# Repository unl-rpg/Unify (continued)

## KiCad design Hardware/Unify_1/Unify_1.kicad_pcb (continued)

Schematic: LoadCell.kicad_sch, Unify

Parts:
C41, C42: 100n; C_0603_1608Metric
R101: 190k; R_0603_1608Metric
R102: 10k; R_0603_1608Metric
U30: INA321

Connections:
+5VA: C42.1, U30.7 (V+), U30.8 (SD); also elsewhere on the board
/Peripherals/LC_3_ADC: C41.1, R101.1, U30.6 (VOUT); also elsewhere on the board
/Peripherals/VREF: R102.2, U30.5 (REF); also elsewhere on the board
GND: C41.2, C42.2, U30.4 (V-); also elsewhere on the board
LC_3_NEG: U30.2 (VIN-); also elsewhere on the board
LC_3_POS: U30.3 (VIN+); also elsewhere on the board
unnamed: R101.2, R102.1, U30.1 (RG)

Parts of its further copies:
C37, C38, C39, C40: 100n; C_0603_1608Metric
R97, R99: 190k; R_0603_1608Metric
R98, R100: 10k; R_0603_1608Metric
U28, U29: INA321

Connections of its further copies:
+5VA: C38.1, C40.1, U28.7 (V+), U28.8 (SD), U29.7 (V+), U29.8 (SD); also elsewhere on the board
/Peripherals/LC_1_ADC: C37.1, R97.1, U28.6 (VOUT); also elsewhere on the board
/Peripherals/LC_2_ADC: C39.1, R99.1, U29.6 (VOUT); also elsewhere on the board
/Peripherals/VREF: R98.2, R100.2, U28.5 (REF), U29.5 (REF); also elsewhere on the board
GND: C37.2, C38.2, C39.2, C40.2, U28.4 (V-), U29.4 (V-); also elsewhere on the board
LC_1_NEG: U28.2 (VIN-); also elsewhere on the board
LC_1_POS: U28.3 (VIN+); also elsewhere on the board
LC_2_NEG: U29.2 (VIN-); also elsewhere on the board
LC_2_POS: U29.3 (VIN+); also elsewhere on the board
unnamed: R97.2, R98.1, U28.1 (RG)
unnamed: R99.2, R100.1, U29.1 (RG)

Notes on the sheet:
Calculations: Load Cell Rated Output: 1.5 +- 0.5 mV/V Load Cell Rated Output at 5V Supply: 5 - 10 mV (Calibrate in software) Nominal Load Cell Rated Output: 7.5mV So load cell will register a max 10mV differential signal at max load Instrumentation Amplifier Output: Vout = (Vin+ - Vin-) * Gain Inam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
+5V
Bridge
TAS606 Load Cell: Capacity: 50kg, 200kg (There are more) Rated Output: 1.5 +- 0.5 mV/V Excitation Voltage: 5-15V Output Resistance: 350 +- 3 Ohms V+: Red, V-: Black, Out+: Green, Out-: White
INA321: VOUT = ((VIN+) - (VIN-)) * Gain Gain = 5 + (5 * (R2/R1)) R2: Between Vout and RG R1: Between RG and REF R1 and R2 should have around 200k of combined resistance

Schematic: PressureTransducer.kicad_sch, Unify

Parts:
C47: 100n; C_0603_1608Metric
R107: 150; R_0603_1608Metric

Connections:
GND: C47.2, R107.2; also elsewhere on the board
PT_2: C47.1, R107.1; also elsewhere on the board

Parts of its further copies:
C46: 100n; C_0603_1608Metric
R106: 150; R_0603_1608Metric

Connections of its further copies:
GND: C46.2, R106.2; also elsewhere on the board
PT_1: C46.1, R106.1; also elsewhere on the board

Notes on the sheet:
2 Wire Pressure Transducer
4 Wire Pressure Transducer
+12V
Pressure Transducers: Achcroft E2GA5NM0242FCX03F1000# 1000PSI, 9-36V, 4-20mA,-40-125C Ashcroft E2GA5NM0242FCX03F150# 150PSI, 9-36V, 4-20mA,-40-125C
Sense
3 Wire Pressure Transducer
Use 4-20mA Transmitting Pressure Transducers These have a proportional current output signal Signal can be read through a shunt resistor as a voltage These come in a few common configurations. 2 Wire: Place in series with shunt resistor 3 Wire: Power with 12V and connect output to the shunt resisto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
Input Current: 4 - 20mA Output Voltage: 0.6 - 3V Shunt Resistor: 150 Ohms

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
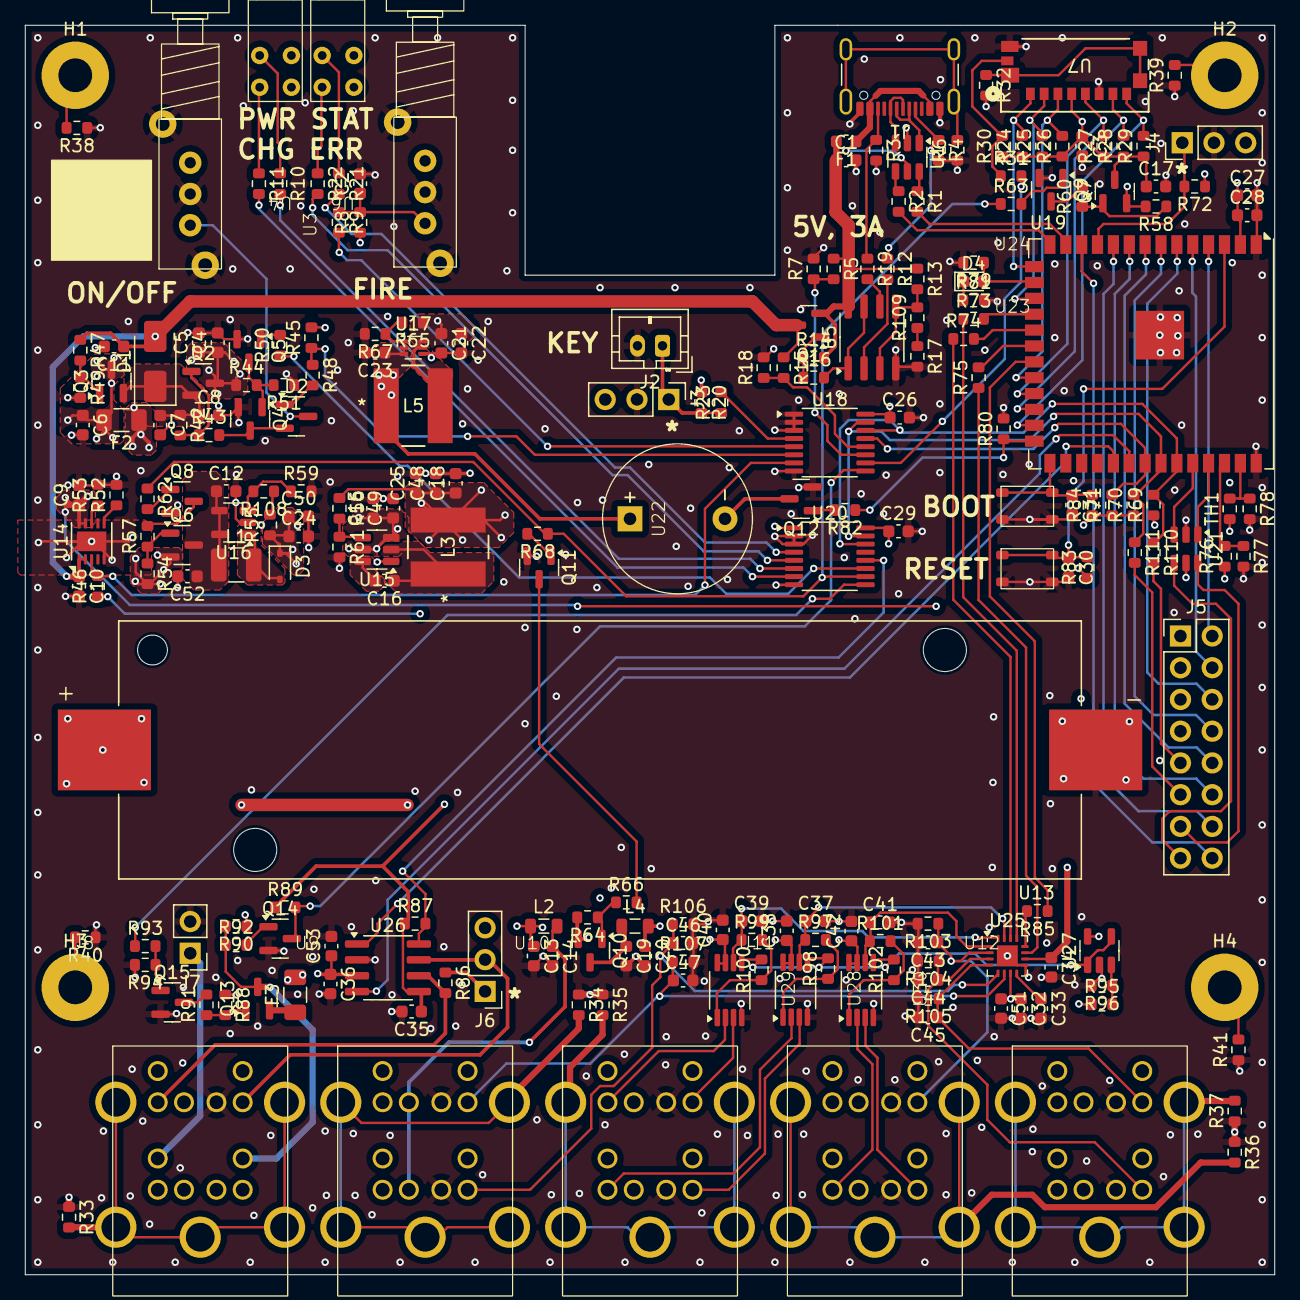
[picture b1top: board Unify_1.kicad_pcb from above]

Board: 4 copper layers, 100.0 x 100.0 mm, 233 parts (0 on the bottom side), 163 nets.

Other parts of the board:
Q6: DMG2305UZ; SOT-23
Q8: MMBT3904; SOT-23
R54: 100k; R_0603_1608Metric
R57: 1k; R_0603_1608Metric

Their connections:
GND: Q8.2 (E); also elsewhere on the board
unnamed: Q6.1 (G), R54.1, R57.1
unnamed: Q8.3 (C), R57.2

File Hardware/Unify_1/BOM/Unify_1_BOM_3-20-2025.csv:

Reference,Value,Datasheet,Footprint,Qty,DNP
"C1,C7,C12,C32,C33,C34",2.2u,~,Capacitor_SMD:C_0603_1608Metric,6,
"C2,C3,C8,C9,C10,C11,C15,C16,C26,C28,C29,C30,C31,C35,C36,C37,C38,C39,C40,C41,C42,C43,C44,C45,C46,C47",100n,~,Capacitor_SMD:C_0603_1608Metric,26,
"C4,C5,C6,C18,C21,C22,C25,C48,C49,C52",22u,~,Capacitor_SMD:C_0603_1608Metric,10,
"C13,C14,C24,C50","10u, 16V",~,Capacitor_SMD:C_0603_1608Metric,4,
"C17,C19,C20,C23,C27,C51,C53,L2,L4",10u,~,-- mixed values --,9,
"D1,F1,F2",3A,~,-- mixed values --,3,
D2,BAT54C,http://www.diodes.com/_files/datasheets/ds11005.pdf,Package_TO_SOT_SMD:SOT-23,1,
D3,200mA,~,Diode_SMD:D_SOD-323,1,
D4,RED,~,LED_SMD:LED_0603_1608Metric,1,
F3,2A,~,Fuse:Fuse_1206_3216Metric,1,
J1,USB_C_Receptacle_USB2.0_16P,https://www.usb.org/sites/default/files/documents/usb_type-c.zip,Connector_USB:USB_C_Receptacle_GCT_USB4105-xx-A_16P_TopMnt_Horizontal,1,
J2,JST_PH-B2B,~,Connector_JST:JST_PH_B2B-PH-K_1x02_P2.00mm_Vertical,1,
"J3,J4,J6",2.54mm_PinHeader,~,Connector_PinHeader_2.54mm:PinHeader_1x03_P2.54mm_Vertical,3,
J5,Conn_02x08_Odd_Even,~,Connector_PinHeader_2.54mm:PinHeader_2x08_P2.54mm_Vertical,1,
J7,2.54mm_PinHeader,~,Connector_PinHeader_2.54mm:PinHeader_1x02_P2.54mm_Vertical,1,DNP
L1,"BRL3225T100K, 10u, 420m",~,Inductor_SMD:L_1210_3225Metric,1,
L3,"SRN6045-3R3Y, 3.3u",~,Unify:IND_BOURNS_SRN6045,1,
L5,"SRN6045-1R0Y, 1.0u",~,Unify:IND_BOURNS_SRN6045,1,
"Q1,Q2,Q3,Q6,Q7,Q10,Q13",DMG2305UZ,,Package_TO_SOT_SMD:SOT-23,7,
"Q4,Q5,Q8,Q9,Q11,Q12,Q14,Q15",MMBT3904,https://www.onsemi.com/pdf/datasheet/pzt3904-d.pdf,Package_TO_SOT_SMD:SOT-23,8,
"R1,R2,R6,R32,R33,R34,R35,R36,R37,R38,R39,R40,R41,R73,R74,R75,R85,R110,R111",0,~,Resistor_SMD:R_0603_1608Metric,19,
"R3,R4,R5,R15",5k1,~,Resistor_SMD:R_0603_1608Metric,4,
"R7,R8,R12,R17,R18,R19,R20,R24,R25,R26,R27,R28,R29,R30,R44,R45,R46,R50,R53,R55,R61,R62,R63,R68,R72,R76,R77,R78,R79,R80,R83,R84,R87,R89,R90,R92,R94,R95,R96,R98,R100,R102,R103,R104,R105,R108,TH1",10k,~,Resistor_SMD:R_0603_1608Metric,47,
"R9,R16,R23,R31,R43,R47,R48,R52,R57,R60,R66,R91,R93,R109",1k,~,Resistor_SMD:R_0603_1608Metric,14,
"R10,R11,R21,R22,R59,R69,R70,R71,R81,R82",2k,~,Resistor_SMD:R_0603_1608Metric,10,
"R13,R56",33k,~,Resistor_SMD:R_0603_1608Metric,2,
"R14,R42,R51,R54,R58,R64,R67,R88",100k,~,Resistor_SMD:R_0603_1608Metric,8,
R49,50k,~,Resistor_SMD:R_0603_1608Metric,1,
R65,732k,~,Resistor_SMD:R_0603_1608Metric,1,
R86,120,~,Resistor_SMD:R_0603_1608Metric,1,
"R97,R99,R101",190k,~,Resistor_SMD:R_0603_1608Metric,3,
"R106,R107",150,~,Resistor_SMD:R_0603_1608Metric,2,
"U1,U21",USBLC6-2SC6,https://www.st.com/resource/en/datasheet/usblc6-2.pdf,Package_TO_SOT_SMD:SOT-23-6,2,
"U2,U3",PN11SHNA03QE,,Unify:PN11SHNA03QE,2,
"U4,U6",SSF-LXH240GGD,,Unify:SSF-LXH240GGD,2,
U5,LM2903,http://www.ti.com/lit/ds/symlink/lm393.pdf,Package_SO:SOIC-8_3.9x4.9mm_P1.27mm,1,
U7,475710001,,Unify:47571-0001_MOL,1,
"U8,U9,U10,U11,U12",KMDGX-6S-6S-S4N1,,Unify:KMDGX-6S-6S-S4N1,5,
U13,1042P,,Unify:BAT_1042P,1,
U14,MCP73833-xxx-MF,https://ww1.microchip.com/downloads/aemDocuments/documents/O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,Package_DFN_QFN:DFN-10-1EP_3x3mm_P0.5mm_EP1.58x2.35mm,1,
U15,TPS562201,,Package_TO_SOT_SMD:SOT-23-6,1,
U16,MIC2288,,Package_TO_SOT_SMD:TSOT-23-5,1,
U17,TPS61023,,Package_TO_SOT_SMD:SOT-563,1,
"U18,U20",TCA9534,http://www.ti.com/lit/ds/symlink/tca9534.pdf,Package_SO:TSSOP-16_4.4x5mm_P0.65mm,2,
U19,ESP32-S3-WROOM-1U-N16R2,https://www.espressif.com/sites/default/files/documentation/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,RF_Module:ESP32-S3-WROOM-1U,1,
U22,CMI-1275C-050,,Unify:CMI-1275C-050,1,
"U23,U24",PTS815SJM250SMTRLFS,,Unify:PTS815SJM250SMTRLFS,2,
U25,ADS7028,,Package_DFN_QFN:WQFN-16-1EP_3x3mm_P0.5mm_EP1.68x1.68mm,1,
U26,ATA6561,,Package_SO:SOIC-8_3.9x4.9mm_P1.27mm,1,
U27,MCP6006,,Package_TO_SOT_SMD:SOT-23-5,1,
"U28,U29,U30",INA321,,Unify:INA321,3,

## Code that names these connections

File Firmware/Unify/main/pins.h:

/********************************************************************************
 * File Name          : pins.h
 * Author             : Jack Shaver
 * Date               : 4/1/2025
 * Description        : Definitions of IO Pins
 ********************************************************************************/

#ifndef pins_h
#define pins_h
 
#ifdef __cplusplus
extern "C" {
#endif

// GPIO Pins Definitions
#define BUTTON_PIN 0
#define CONFIG_PIN 18
#define BUZZER_PIN 45
#define BLINK_PIN 46

// ADC Pins Definitions
#define PCB_TEMP_ADC_PIN 1
#define BATTERY_VOLT_ADC_PIN 2

// SD Card Pins Definitions
#define SD_CARD_D0_PIN 47
#define SD_CARD_D1_PIN 48
#define SD_CARD_D2_PIN 3
#define SD_CARD_D3_PIN 9
#define SD_CARD_CMD_PIN 14
#define SD_CARD_CLK_PIN 21

// I2C Pins Definitions
#define I2C_INTERRUPT_PIN 40
#define I2C_SDA_PIN 41
#define I2C_SCL_PIN 42

// SPI Pins Definitions
// NOTE THAT THERE WAS AN ERROR WITH THE SCHEMATIC
// had to swap clk and cs here
#define SPI_CS_PIN 12
#define SPI_MOSI_PIN 11
#define SPI_CLK_PIN 10
#define SPI_MISO_PIN 13

// TWAI Pins Definitions
#define TWAI_TX_PIN 38
#define TWAI_RX_PIN 39

// Expansion Pins Definitions
#define EXP_0_PIN 4
#define EXP_1_PIN 5
#define EXP_2_PIN 6
#define EXP_3_PIN 7
#define EXP_4_PIN 15
#define EXP_5_PIN 16
#define EXP_6_PIN 17
#define EXP_7_PIN 8

#ifdef __cplusplus
}
#endif
 
#endif 
 

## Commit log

2025-05-09 Initial Commit. This is the copy which worked during testing in spring 2025. Need to modify the console interface, improve the ADC reading to be sequential, and fix the power off failures.
